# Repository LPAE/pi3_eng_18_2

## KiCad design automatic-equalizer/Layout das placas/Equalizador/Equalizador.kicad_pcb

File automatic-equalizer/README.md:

# Elaboração de um Sistema de Auto-Equalização Ambiente
O projeto proposto é um sistema de equalização sonora automática utilizando equalizadores analógicos cujos ganhos de cada banda são controlados por uma tensão proveniente de um microcontrolador. Esses ganhos irão variar conforme os aspectos mecânicos da sala, tais como material da parede e móveis posicionados em diferentes lugares, fazendo com que o espectro de frequências de áudio antes não linear em decorrência das perdas ocasionadas, se torne linear. O esquema inicial proposto ao projeto é o presente na Figura 1.

#### Figura 1 - Esquema inicial do projeto.

#### <i>A descrição completa do projeto está no arquivo [relatorio_final.pdf](https://github.com/BroeringFelipe/automatic-equalizer/blob/master/Relat%C3%B3rio%20do%20Projeto/Relat%C3%B3rio%20Final.pdf)</i>

### Bibliografia
ANALOG DEVICES: <b>Programmable Gain Amplifiers</b>. 2018. Disponível em: <https://www.analog.com/en/products/amplifiers/specialty-amplifiers/programmable-gain-amplifiers.html>. Acesso em: 14 dez. 2018.

TEXAS INSTRUMENTS: <b>Datasheet, PGA103 - Programmable Gain Amplifier</b>. 1993. Disponível em: <http://www.ti.com/lit/ds/sbos031/sbos031.pdf>. Acesso em: 14 dez. 2018.

FAIRCHILD Semiconductor Corporation:<b> A Linear Gain Controlled Amplifier, Amplication Note</b>. Rev. 1.0. 2015. Disponível em: <http://www.ti.com/lit/ds/sbos031/sbos031.pdf>. Acesso em: 14 dez. 2018.

CARTER,  B.;  MANCINI,  R.<b> Op  Amps  For  Everyone</b>.  3.  ed.  Burlington,  MA,  USA:  Elsevier,2004. 

RIBEIRO, Renan.<b> Desenvolvimento de um Equalizador Gráfico Digital de 10 Bandas</b>. 2017. 54 f. Trabalho de conclusão de curso (Curso de Engenharia de Computação) - Universidade Tecnológica Federal do Paraná, Pato Branco, 2017.

STMICROELECTRONICS TDA7294: <b>100V - 100W DMOS AUDIO AMPLIFIER WITH MUTE/ST-BY - Datasheet</b>. 2003. Disponível em: <https://www.st.com/resource/en/datasheet/cd00000017.pdf>. Acesso em: 11 dez. 2018.

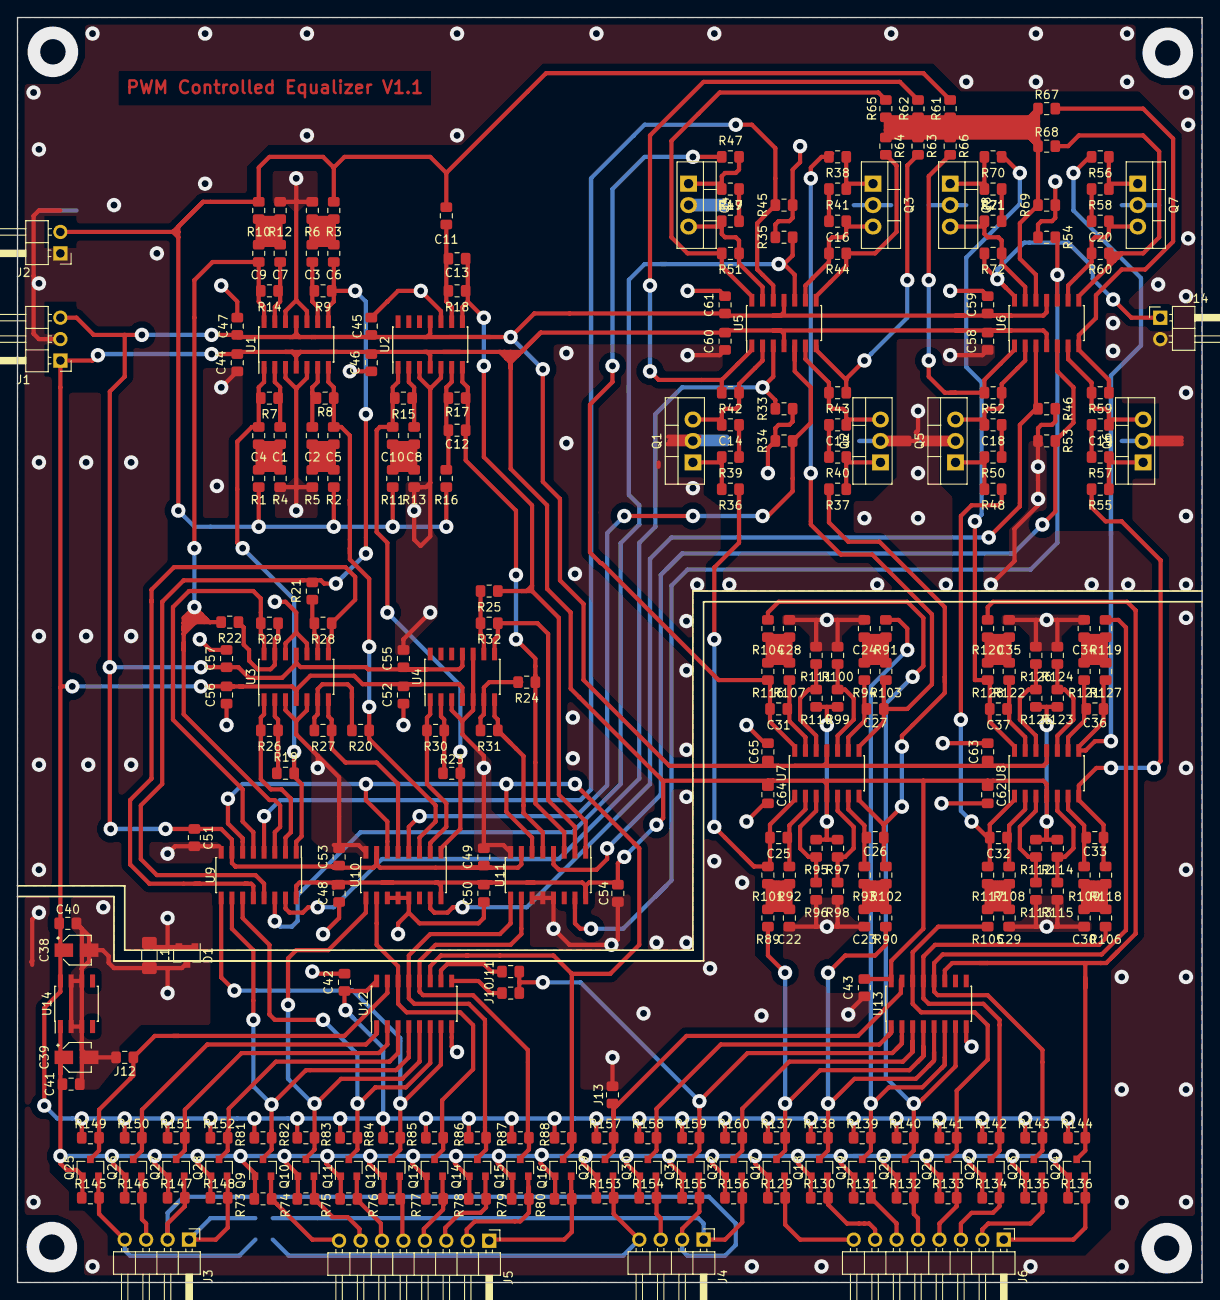
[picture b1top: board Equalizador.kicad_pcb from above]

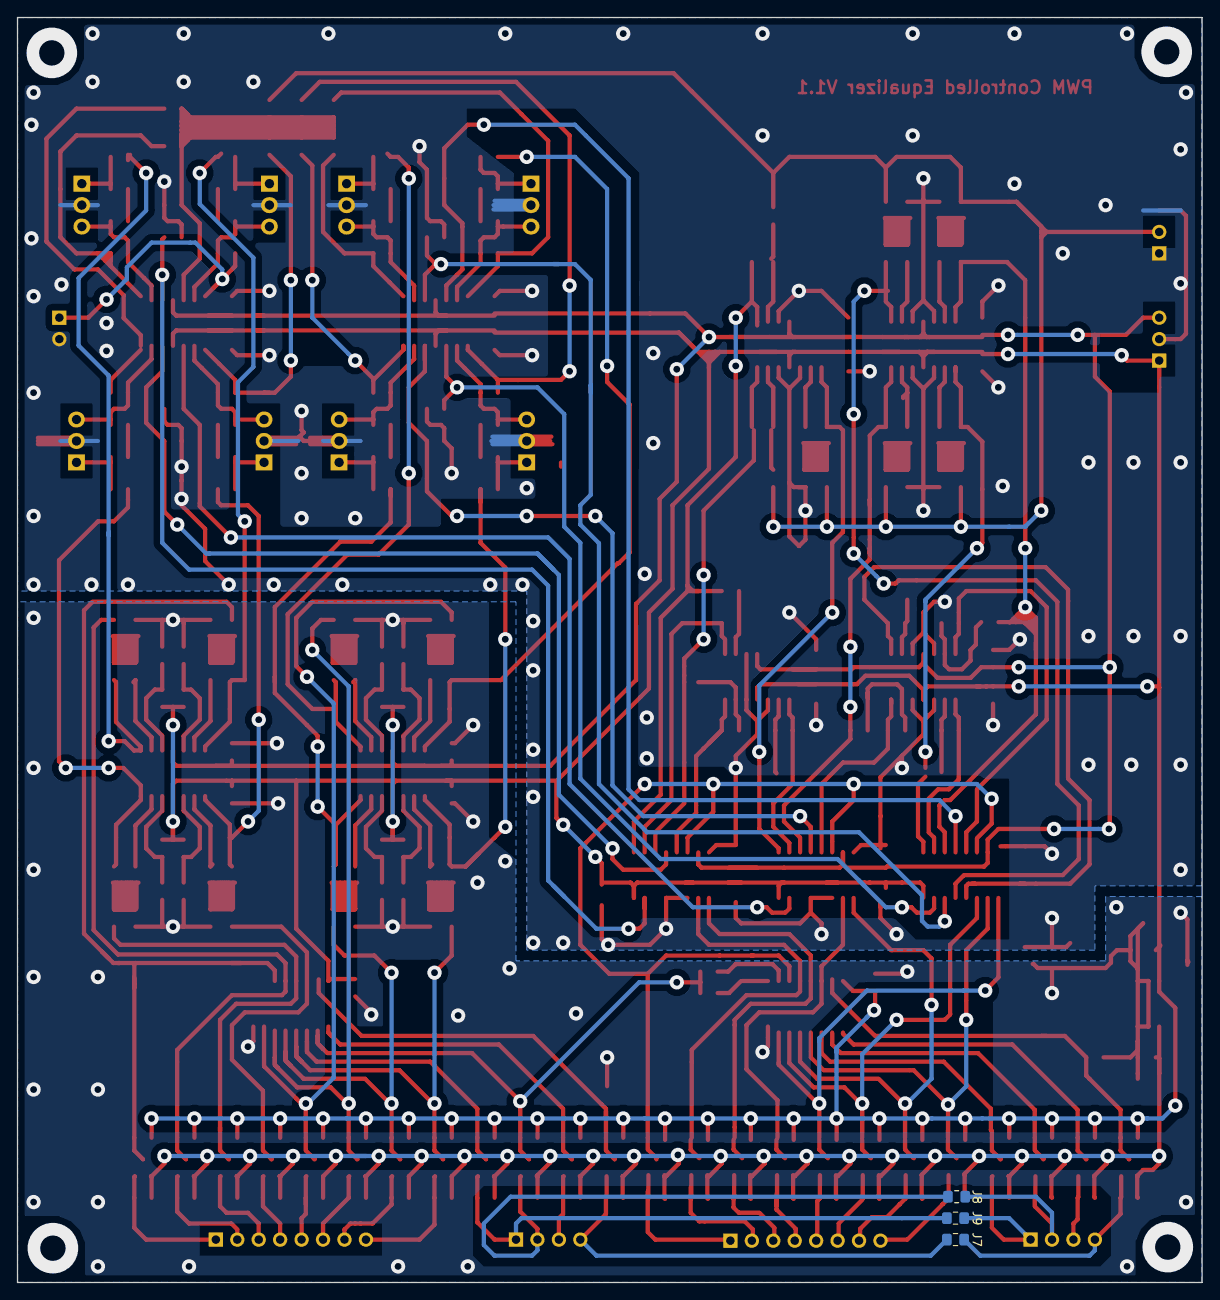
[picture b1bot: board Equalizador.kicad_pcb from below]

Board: 2 copper layers, 140.3 x 149.9 mm, 287 parts (3 on the bottom side), 161 nets.

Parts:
C1, C2, C3, C4, C5, C6, C7, C8, C9, C10, C11, C12, C13, C14, C15, C16, C17, C18, C19, C20, C21, C22, C23, C24, C25, C26, C27, C28, C29, C30, C31, C32, C33, C34, C35, C36, C37, C40, C41, C42, C43, C44, C45, C46, C47, C48, C49, C50, C51, C52, C53, C54, C55, C56, C57, C58, C59, C60, C61, C62, C63, C64, C65: C_Small; C_0805_2012Metric_Pad1.15x1.40mm_HandSolder
C38, C39: C_Small; CP_Elec_3x5.3
D1: BAT54S; SOT-23
J1: Conn_01x03; PinHeader_1x03_P2.54mm_Horizontal
J2, J14: Conn_01x02; PinHeader_1x02_P2.54mm_Horizontal
J3, J4: Conn_01x04; PinHeader_1x04_P2.54mm_Horizontal
J5, J6: Conn_01x08; PinHeader_1x08_P2.54mm_Horizontal
J7, J8, J9, J10, J11, J12, J13: Conn_02x01; R_0805_2012Metric_Pad1.15x1.40mm_HandSolder
L1: L_Small; L_1206_3216Metric_Pad1.42x1.75mm_HandSolder
Q1, Q2, Q3, Q4, Q5, Q6, Q7, Q8: BF245C; TO-220-3_Vertical
Q9, Q10, Q11, Q12, Q13, Q14, Q15, Q16, Q17, Q18, Q19, Q20, Q21, Q22, Q23, Q24, Q25, Q26, Q27, Q28, Q29, Q30, Q31, Q32: 2N7002; SOT-23
R1, R2, R3, R4, R5, R6, R7, R8, R9, R10, R11, R12, R13, R14, R15, R16, R17, R18, R33, R34, R35, R36, R37, R38, R39, R40, R41, R42, R43, R44, R45, R46, R47, R48, R49, R50, R51, R52, R53, R54, R55, R56, R57, R58, R59, R60, R61, R62, R63, R64, R65, R66, R67, R68, R69, R70, R71, R72, R73, R74, R75, R76, R77, R78, R79, R80, R81, R82, R83, R84, R85, R86, R87, R88, R89, R90, R91, R92, R93, R94, R95, R96, R97, R98, R99, R100, R101, R102, R103, R104, R105, R106, R107, R108, R109, R110, R111, R112, R113, R114, R115, R116, R117, R118, R119, R120, R121, R122, R123, R124, R125, R126, R127, R128, R129, R130, R131, R132, R133, R134, R135, R136, R137, R138, R139, R140, R141, R142, R143, R144, R145, R146, R147, R148, R149, R150, R151, R152, R153, R154, R155, R156, R157, R158, R159, R160: R_US; R_0805_2012Metric_Pad1.15x1.40mm_HandSolder
R19, R20, R21, R22, R23, R24, R25, R26, R27, R28, R29, R30, R31, R32: 10k; R_0805_2012Metric_Pad1.15x1.40mm_HandSolder
U1, U2, U3, U4, U5, U6, U7, U8: TL074; SOIC-14_3.9x8.7mm_P1.27mm
U9, U10, U11: 4053; SOIC-16_3.9x9.9mm_P1.27mm
U12, U13: 4094D; SOIC-16_3.9x9.9mm_P1.27mm
U14: L78L33_SO8; SOIC-8_3.9x4.9mm_P1.27mm

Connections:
+3V3: C39.1, C41.1, Q9.1, Q10.1, Q11.1, Q12.1, Q13.1, Q14.1, Q15.1, Q16.1, Q17.1, Q18.1, Q19.1, Q20.1, Q21.1, Q22.1, Q23.1, Q24.1, Q25.1, Q26.1, Q27.1, Q28.1, Q29.1, Q30.1, Q31.1, Q32.1, R73.1, R74.1, R75.1, R76.1, R77.1, R78.1, R79.1, R80.1, R129.1, R130.1, R131.1, R132.1, R133.1, R134.1, R135.1, R136.1, R145.1, R146.1, R147.1, R148.1, R153.1, R154.1, R155.1, R156.1, U14.1
+15V: C38.1, C40.1, C42.1, C43.1, C44.1, C46.1, C48.1, C50.1, C52.2, C54.2, C56.2, C58.1, C60.1, C62.1, C64.1, J1.1, R81.1, R82.1, R83.1, R84.1, R85.1, R86.1, R87.1, R88.1, R95.1, R97.1, R99.1, R110.1, R112.1, R114.1, R123.1, R125.1, R137.1, R138.1, R139.1, R140.1, R141.1, R142.1, R143.1, R144.1, R149.1, R150.1, R151.1, R152.1, R157.1, R158.1, R159.1, R160.1, U1.4, U2.4, U3.4, U4.4, U5.4, U6.4, U7.4, U8.4, U9.16, U10.16, U11.16, U12.16, U13.16, U14.8
-15V: C45.1, C47.1, C49.1, C51.1, C53.2, C55.2, C57.2, C59.1, C61.1, C63.1, C65.1, J1.3, U1.11, U2.11, U3.11, U4.11, U5.11, U6.11, U7.11, U8.11, U9.7, U10.7, U11.7
/Inversoras/Ctrl_inv_1: Q9.3, R81.2, U9.10, U12.4
/Inversoras/Ctrl_inv_2: Q10.3, R82.2, U10.9, U12.5
/Inversoras/Ctrl_inv_3: Q11.3, R83.2, U9.11, U12.6
/Inversoras/Ctrl_inv_4: Q12.3, R84.2, U9.9, U12.7
/Inversoras/Ctrl_inv_5: Q13.3, R85.2, U10.10, U12.14
/Inversoras/Ctrl_inv_6: Q14.3, R86.2, U11.9, U12.13
/Inversoras/Ctrl_inv_7: Q15.3, R87.2, U11.10, U12.12
/Inversoras/INH: Q16.3, R88.2, U9.6, U10.6, U11.6, U12.11
/Inversoras/Vin_1_1: C4.1, R7.1, R19.2, U1.1, U9.1
/Inversoras/Vin_2_1: C5.1, R8.1, R20.2, U1.7, U10.3
/Inversoras/Vin_3_1: C6.1, R9.1, R21.2, U1.8, U9.13
/Inversoras/Vin_4_1: C9.1, R14.1, R22.2, U1.14, U9.3
/Inversoras/Vin_5_1: C10.1, R15.1, R23.2, U2.1, U10.1
/Inversoras/Vin_6_1: C12.1, R17.1, R24.2, U2.7, U11.3
/Inversoras/Vin_7_1: C13.1, R18.1, R25.2, U2.8, U11.1
/Inversoras/Vinv_1: R26.1, U3.1, U9.2
/Inversoras/Vinv_2: R27.1, U3.7, U10.5
/Inversoras/Vinv_3: R28.1, U3.8, U9.12
/Inversoras/Vinv_4: R29.1, U3.14, U9.5
/Inversoras/Vinv_5: R30.1, U4.1, U10.2
/Inversoras/Vinv_6: R31.1, U4.7, U11.5
/Inversoras/Vinv_7: R32.1, U4.8, U11.2
/Somador/Ctrl_G: C37.1, R70.2, R128.1, U8.14
/Somador/Vin_1_3: R42.1, R62.2, U5.1
/Somador/Vin_2_3: R43.1, R63.2, U5.7
/Somador/Vin_3_3: R44.1, R64.2, U5.8
/Somador/Vin_4_3: R51.1, R65.2, U5.14
/Somador/Vin_5_3: R52.1, R66.2, U6.1
/Somador/Vin_6_3: R59.1, R67.2, U6.7
/Somador/Vin_7_3: R60.1, R68.2, U6.8
/Somador/Vout: J14.1, R72.1, U6.14
/VCA/Ctrl_G_1: C25.1, R36.2, R101.1, U7.1
/VCA/Ctrl_G_2: C26.1, R37.2, R102.1, U7.7
/VCA/Ctrl_G_3: C27.1, R38.2, R103.1, U7.8
/VCA/Ctrl_G_4: C31.1, R47.2, R116.1, U7.14
/VCA/Ctrl_G_5: C32.1, R48.2, R117.1, U8.1
/VCA/Ctrl_G_6: C33.1, R55.2, R118.1, U8.7
/VCA/Ctrl_G_7: C36.1, R56.2, R127.1, U8.8
/VCA/Vin_1_2: R33.1, U5.3, U9.15
/VCA/Vin_2_2: R34.1, U5.5, U10.4
/VCA/Vin_3_2: R35.1, U5.10, U9.14
/VCA/Vin_4_2: R45.1, U5.12, U9.4
/VCA/Vin_5_2: R46.1, U6.3, U10.15
/VCA/Vin_6_2: R53.1, U6.5, U11.4
/VCA/Vin_7_2: R54.1, U6.10, U11.15
/sheet5BB14968/OUT1: J12.1, Q25.3, R149.2, U12.15
/sheet5BB14968/OUT2: Q26.3, R150.2, U12.1
/sheet5BB14968/OUT3: Q27.3, R151.2, U12.2
/sheet5BB14968/OUT4: Q28.3, R152.2, U12.3
/sheet5BB62068/OUT1: Q17.3, R89.1, R137.2, U13.4
/sheet5BB62068/OUT2: Q18.3, R90.1, R138.2, U13.5
/sheet5BB62068/OUT3: Q19.3, R91.1, R139.2, U13.6
/sheet5BB62068/OUT4: Q20.3, R104.1, R140.2, U13.7
/sheet5BB62068/OUT5: Q21.3, R105.1, R141.2, U13.14
/sheet5BB62068/OUT6: Q22.3, R106.1, R142.2, U13.13
/sheet5BB62068/OUT7: Q23.3, R119.1, R143.2, U13.12
/sheet5BB62068/OUT8: Q24.3, R120.1, R144.2, U13.11
/sheet5BC68AAF/OUT1: J13.1, Q29.3, R157.2, U13.15
/sheet5BC68AAF/OUT2: Q30.3, R158.2, U13.1
/sheet5BC68AAF/OUT3: J10.2, J11.2, Q31.3, R159.2, U13.2
/sheet5BC68AAF/OUT4: Q32.3, R160.2, U13.3
Ctrl_Inv_1: J5.8, Q9.2, R73.2
Ctrl_Inv_2: J5.7, Q10.2, R74.2
Ctrl_Inv_3: J5.6, Q11.2, R75.2
Ctrl_Inv_4: J5.5, Q12.2, R76.2
Ctrl_Inv_5: J5.4, Q13.2, R77.2
Ctrl_Inv_6: J5.3, Q14.2, R78.2
Ctrl_Inv_7: J5.2, Q15.2, R79.2
Ctrl_Inv_8: J5.1, Q16.2, R80.2
Ctrl_Inv_CLK: J3.1, J9.1, Q28.2, R148.2
Ctrl_Inv_DATA: J3.2, J8.1, Q27.2, R147.2
Ctrl_Inv_OE: J3.4, J7.1, Q25.2, R145.2
Ctrl_Inv_STR: J3.3, Q26.2, R146.2
GND: C44.2, C45.2, C46.2, C47.2, C48.2, C49.2, C50.2, C51.2, C52.1, C53.1, C54.1, C55.1, C56.1, C57.1, C58.2, C59.2, C60.2, C61.2, D1.1, D1.2, J1.2, J2.1, J14.2, L1.1, Q1.2, Q2.2, Q3.2, Q4.2, Q5.2, Q6.2, Q7.2, Q8.2, R4.1, R5.1, R6.1, R12.1, R13.1, R33.2, R34.2, R35.2, R45.2, R46.2, R53.2, R54.2, R69.2, U1.3, U1.5, U1.10, U1.12, U2.3, U2.5, U2.10, U3.3, U3.5, U3.10, U3.12, U4.3, U4.5, U4.10, U9.8, U10.8, U10.11, U10.12, U10.13, U11.8, U11.11, U11.12, U11.13
GNDD: C22.1, C23.1, C24.1, C28.1, C29.1, C30.1, C34.1, C35.1, C38.2, C39.2, C40.2, C41.2, C42.2, C43.2, C62.2, C63.2, C64.2, C65.2, D1.3, J12.2, J13.2, L1.2, R96.2, R98.2, R100.2, R111.2, R113.2, R115.2, R124.2, R126.2, U12.8, U13.8, U14.2, U14.3, U14.6, U14.7
unnamed: C1.1, R7.2, U1.2
unnamed: C1.2, C4.2, R1.2, R4.2
unnamed: C2.1, R8.2, U1.6
unnamed: C2.2, C5.2, R2.2, R5.2
unnamed: C3.1, R9.2, U1.9
unnamed: C3.2, C6.2, R3.2, R6.2
unnamed: C7.1, R14.2, U1.13
unnamed: C7.2, C9.2, R10.2, R12.2
unnamed: C8.1, R15.2, U2.2
unnamed: C8.2, C10.2, R11.2, R13.2
unnamed: C11.1, C13.2, R18.2, U2.9
unnamed: C12.2, R16.2, R17.2, U2.6
unnamed: C14.1, Q1.3, R42.2, U5.2
unnamed: C14.2, R39.1
unnamed: C15.1, Q2.3, R43.2, U5.6
unnamed: C15.2, R40.1
unnamed: C16.1, Q3.3, R44.2, U5.9
unnamed: C16.2, R41.1
unnamed: C17.1, Q4.3, R51.2, U5.13
unnamed: C17.2, R49.1
unnamed: C18.1, Q5.3, R52.2, U6.2
unnamed: C18.2, R50.1
unnamed: C19.1, Q6.3, R59.2, U6.6
unnamed: C19.2, R57.1
unnamed: C20.1, Q7.3, R60.2, U6.9
unnamed: C20.2, R58.1
unnamed: C21.1, Q8.3, R72.2, U6.13
unnamed: C21.2, R71.1
unnamed: C22.2, R89.2, R92.2, R101.2
unnamed: C23.2, R90.2, R93.2, R102.2
unnamed: C24.2, R91.2, R94.2, R103.2
unnamed: C25.2, R92.1, U7.2
unnamed: C26.2, R93.1, U7.6
unnamed: C27.2, R94.1, U7.9
unnamed: C28.2, R104.2, R107.2, R116.2
unnamed: C29.2, R105.2, R108.2, R117.2
unnamed: C30.2, R106.2, R109.2, R118.2
unnamed: C31.2, R107.1, U7.13
unnamed: C32.2, R108.1, U8.2
unnamed: C33.2, R109.1, U8.6
unnamed: C34.2, R119.2, R121.2, R127.2
unnamed: C35.2, R120.2, R122.2, R128.2
unnamed: C36.2, R121.1, U8.9
unnamed: C37.2, R122.1, U8.13
unnamed: J10.1, U12.9
unnamed: J11.1, U12.10
unnamed: Q1.1, R36.1, R39.2
unnamed: Q2.1, R37.1, R40.2
unnamed: Q3.1, R38.1, R41.2
unnamed: Q4.1, R47.1, R49.2
unnamed: Q5.1, R48.1, R50.2
unnamed: Q6.1, R55.1, R57.2
unnamed: Q7.1, R56.1, R58.2
unnamed: Q8.1, R70.1, R71.2
unnamed: R19.1, R26.2, U3.2
unnamed: R20.1, R27.2, U3.6
unnamed: R21.1, R28.2, U3.9
unnamed: R22.1, R29.2, U3.13
unnamed: R23.1, R30.2, U4.2
unnamed: R24.1, R31.2, U4.6
unnamed: R25.1, R32.2, U4.9
unnamed: R61.1, R62.1, R63.1, R64.1, R65.1, R66.1, R67.1, R68.1, R69.1, U6.12
unnamed: R95.2, R96.1, U7.3
unnamed: R97.2, R98.1, U7.5
unnamed: R99.2, R100.1, U7.10
unnamed: R110.2, R111.1, U7.12
unnamed: R112.2, R113.1, U8.3
unnamed: R114.2, R115.1, U8.5
unnamed: R123.2, R124.1, U8.10
unnamed: R125.2, R126.1, U8.12
PWM_1: J6.8, Q17.2, R129.2
PWM_2: J6.7, Q18.2, R130.2
PWM_3: J6.6, Q19.2, R131.2
PWM_4: J6.5, Q20.2, R132.2
PWM_5: J6.4, Q21.2, R133.2
PWM_6: J6.3, Q22.2, R134.2
PWM_7: J6.2, Q23.2, R135.2
PWM_8: J6.1, Q24.2, R136.2
PWM_CLK: J4.1, J9.2, Q32.2, R156.2
PWM_DATA: J4.2, J8.2, Q31.2, R155.2
PWM_OE: J4.4, J7.2, Q29.2, R153.2
PWM_STR: J4.3, Q30.2, R154.2
Vin: C11.2, J2.2, R1.1, R2.1, R3.1, R10.1, R11.1, R16.1, R61.2

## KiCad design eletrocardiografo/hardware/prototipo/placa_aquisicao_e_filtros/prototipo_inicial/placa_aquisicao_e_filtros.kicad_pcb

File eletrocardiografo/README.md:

# Eletrocardiógrafo

Projeto para a disciplina PIN22107 do curso de Graduação em Engenharia Eletrônica do Instituto Federal de Santa Catarina. Consiste na concepção e execução de um eletrocardiógrafo de baixo consumo energético capaz de adquirir um sinal de eletrocardiograma por meio de 3 eletrodos e enviar suas medições para um aplicativo de aparelho celular.

## Especificações de projeto
* Energizado por bateria, portanto apresentando baixo consumo energético.

* Capaz de medir sinais entre 0,05 e 100 Hz, permitindo visualização e análise da morfologia do sinal cardíaco humano com propriedade.

## Etapas do projeto
* **Aquisição do sinal:** Por meio de eletrodos conectados ao paciente, verificando e garantindo a proteção do mesmo, com processo de isolamento do sistema. Os sinais obtidos diretamente dos eletrodos tem amplitude reduzida, atingindo 1 mV com uma frequência na faixa entre 0,05 e 100 Hz. Desse modo, para uma melhor visualização e manipulação, uma etapa de amplificação é necessária, tomando cuidado com a rejeição de ruído de modo comum.

* **Filtros:** Um filtro passa faixa deve ser implementado para seleção da banda de operação desejada, podendo ser composto por um passa altas em série com um passa baixas e, além disso, deve-se atentar para o fato de que a frequência da rede elétrica pode interferir no sinal e, portanto, deve ser removida por meio de um filtro rejeita faixa, com alto fator de qualidade.

* **Adequação do sinal:** Além de um ajuste de offset, é necessário implementar um controle de ganho que adeque a amplitude do sinal, preparando-o para digitalização por meio de um ADC.

* **Digitalização:**  A conversão do sinal analógico para digital pode ser realizada através de um conversor dedicado ou até mesmo por meio do conversor integrado de algum microcontrolador, como por exemplo o ATMEGA328p.

* **Processamento digital:** Envio dos dados via Bluetooth para o aplicativo de celular.

## Fluxograma
Para uma melhor organização e visualização das etapas necessárias, foi construído o seguinte fluxograma:

## Aquisição do sinal
Contando com um amplificador de instrumentação de alta relação sinal-ruído (SNR), o estágio inicial de amplificação faz a leitura do sinal diferencial entre os eletrodos esquerdo e direito, ao mesmo tempo que injeta uma referência por meio de um terceiro eletrodo conectado ao paciente.

O esquemático do circuito utilizado nesse estágio pode ser verificado a seguir, sendo baseado no circuito proposto e verificado na folha de dados do próprio fabricante:

## Filtros
Os filtros passa-baixas, passa-altas e rejeita-faixa foram projetados conforme o equacionamento descrito pelo livro "Amplificadores Operacionais e Filtros Ativos". As simulações foram realizadas no _software_ LTspice XVII. Foi definido inicialmente ganho unitário para todos os filtros.

### Passa-altas
Projetou-se o filtro passa-altas com ganho unitário na estrutura _voltage-controlled voltage source_ (VCVS).

Por meio do uso do software de simulação, o comportamento resultante do filtro é:

### Passa-baixas
Abaixo é possível seguir a sequência de passos utilizados na construção do filtro passa-baixas:

No intuito de otimizar a eficiência energética do eletrocardiógrafo, foi analisada a possibilidade de implementar um filtro passa-baixas passivo, portanto foi realizada uma comparação entre o filtro projetado de 2ª ordem com um filtro passivo na simulação.

Apesar da economia de componentes apresentada pelo filtro passivo, sua atenuação na banda passante é indesejada e, portanto, optou-se pela utilização do filtro de 2ª ordem, que apresenta ainda decaimento de 40 dB por década na rejeição e consequentemente um fator de qualidade mais elevado.

### Rejeita-faixa

Inicialmente, projetou-se o filtro notch ativo para rejeitar ruídos oriundos da rede elétrica de 60 Hz.

Entretanto, devido à sensibilidade deste filtro aos valores dos componentes utilizados, e a necessidade de um elevado fator de qualidade, concluiu-se que implementá-lo digitalmente seria uma alternativa mais apropriada. Além disso, pelo fato do circuito ser alimentado via bateria, a interferência da rede é fortemente reduzida, embora não completamente eliminada.

## Automatic Gain Control (AGC)

Ao longo do projeto, verificou-se que seria interessante a implementação de um ajuste de ganho automático devido à incerteza na amplitude do sinal de entrada, já que o mesmo varia conforme o biotipo do paciente e disposição dos eletrodos, possibilitando que a amplificação seja insuficiente ou demasiada.

Após analisar e estudar diversas maneiras de implementar um sistema de adequação do sinal, buscando obter uma excursão adequada e constante para diferentes amplitudes de entrada, surgiu como uma solução conveniente a ideia de um controle de ganho automático (AGC) por meio de um amplificador operacional não-inversor com a resistência de um JFET participando de sua realimentação negativa e influenciando diretamente em seu ganho de amplificação.

Embora seja possível controlar a resistência do JFET apropriadamente através da aplicação de um PWM gerado pelo microcontrolador que adquire o sinal, isso exige mais processamento do mesmo e consequentemente eleva seu consumo energético. Sendo assim, a alternativa escolhida foi a de controlar esse sistema de maneira analógica.

Com o auxílio do LTSpice, traçou-se, em simulação, a curva da resistência Rds em função da tensão Vgs do BF245B, transistor selecionado para o circuito.

É notável a grande variação em sua resistência que ocorre em um pequeno intervalo de variação de Vgs. Devido a isso, percebe-se que é por volta desse intervalo que o JFET deve operar. Logo, projetou-se um circuito para fechar a malha de realimentação do AGC, constituído de um retificador de precisão inversor com ajuste de ganho, que detecta e inverte a tensão de pico positiva do sinal, mantendo o valor negativo obtido, utilizado para controlar o estrangulamento no canal do transistor, controlando sua condutividade. 

O ajuste de ganho da realimentação, proporcionado pelo trimpot RV1, permite que se encontre o ponto ideal de operação do BF245B e também possibilita a definição de um valor limite para o sinal amplificado pelo AGC.

## Somador

Na intenção de adequar o sinal de saída para uma conversão AD fez com que surgisse a necessidade de inserir um deslocamento de nível no sinal de saída, o deixando completamente positivo. A maneira mais eficiente encontrada faz o uso de um circuito somador não-inversor, visto na figura a seguir:

Mesmo que várias fontes tratem o circuito inversor como mais indicado e até mesmo mais difundido, a escolha pela utilização de um somador não-inversor procurou manter a ideia de um estágio genérico entre os outros, sem levar em conta se o sinal que entrava nele era invertido ou não, já que a presença de um sinal invertido na saída pode ser corrigida com a simples inversão dos conectores dos eletrodos.

Outra parte importante no projeto do somador se deu pela adição de dois resistores de alto valor (1 Megaohm), de maneira a proporcionar um casamento entre as impedâncias de saída do AGC (a própria impedância de saída do amplificador utilizado) e a de entrada do somador (entrada do amplificador empregado).

## Hardware

* **Protótipo inicial**

Em um primeiro momento, para validar os circuitos projetados até aquele momento, optou-se pela confecção de um protótipo contendo apenas os estágios de aquisição e filtragem do sinal. Já na intenção de condicioná-lo para uma conversão AD, por meio de um microcontrolador, existiu a necessidade de um ajuste de _offset_, tornando o sinal de saída completamente positivo. 

A alternativa aparentemente mais prática e econômica foi a de inserir esse acréscimo no valor de tensão já no próprio filtro passa-altas, considerando que a topologia de um filtro ativo MFB (_Multiple Feedback_) permite um deslocamento do nível de tensão apenas injetando a tensão desejada na entrada não-inversora do amplificador operacional envolvido no circuito. Ao contrário do esperado, o _offset_ não se comportou corretamente, pois mesmo com ganho unitário nos filtros seguintes, o sinal de saída apresentou grande instabilidade.

Além disso, o ajuste de ganho do sistema foi inserido por meio de um potenciômetro em série com o resistor de ganho do AD620. Observou-se, entretanto, que essa topologia deixa a desejar pelos valores de ganho muito elevados para esse estágio, já que nele o sinal ainda não foi filtrado e portanto componentes em frequências indesejadas também são amplificadas.

Para ilustrar, a seguir, é possível ver o esquemático que descreve o circuito utilizado no protótipo inicial:

Percebe-se que o circuito é energizado por uma alimentação simétrica de 9V, proveniente de duas baterias. Ainda, abaixo é possível ver o layout da placa de circuito impresso resultante:

* **Placa final**

Levando em conta os problemas encontrados no protótipo inicial, a solução adotada com relação ao _offset_ foi de aplicá-lo em um estágio próprio, consistindo de um somador não-inversor, só no final do circuito, evitando que esse deslocamento de nível de tensão atrapalhasse o funcionamento das etapas anteriores, como os filtros e o próprio AGC.

Pensando no consumo energético e estabilidade do sistema, foi estabelecido que todos os circuitos seriam energizados com alimentação simétrica regulada de 3.3V. Por conseguinte, foi introduzida uma regulação da tensão de alimentação positiva utilizando o regulador linear _low-dropout_ LM1117. Em sequência, visando praticidade, projetou-se a obtenção da tensão de alimentação negativa através do inversor TPS60401. Isso flexibilizou o sistema com relação a sua tensão de entrada, podendo ser energizado por uma única bateria de valor de tensão entre 4.75 e 10V.

Outro ponto importante na construção e adequação do funcionamento da nova placa desenvolvida, consistiu na seleção dos ganhos envolvidos em cada etapa de maneira a manter um valor final de amplificação equilibrado que não trouxesse instabilidade ao conjunto. Um exemplo disso foi o ganho definido para o estágio do amplificador de instrumentação.

Por apresentar uma característica de amplificação com alta relação sinal-ruído (SNR), pareceu interessante o estabelecimento do maior ganho possível nesse estágio, de maneira a eliminar ao máximo o ruído do sinal adquirido. A seleção do ganho do circuito de aquisição é diretamente dependente do valor de resistência selecionado para o resistor R9, entre os pinos 1 e 8 do AD620 (estágio de aquisição). Na intenção de deixar o sistema independente de um ajuste manual, antes regulado pelo potenciômetro adicionado, a ideia passou a ser de fixar o valor desse resistor, inicialmente 75 ohms, resultando em um ganho próximo a 660. 

Com esse ganho estabelecido, a aquisição do sinal se deu de maneira eficiente, apresentando uma boa amplitude para o sinal de saída e uma satisfatória atenuação do ruído envolvido. Com a adição dos filtros, o sinal de saída alcançou as características desejadas para o circuito.

A partir da decisão de adicionar o estágio de controle de ganho, este proporcionou certas limitações em relação ao sinal condicionado pelos primeiros estágios: com um funcionamento adequado do AGC apenas para sinais de entrada com valores de tensão entre 50 e 500 mVpp, o ganho definido para o estágio de aquisição se tornou absurdo, já que o sinal fornecido ao estágio de controle automático de ganho já se encontrava fora dos limites determinados, deixando o sinal de saída instável e oscilando entre as saturações negativa e positiva do amplificador operacional, demonstrando um valor exagerado de amplificação.

Desse modo, ajustes foram feitos e um novo resistor tomou o lugar do R9, com valor igual a 1 kohms, resultando em um ganho próximo a 50 e permitindo que o ganho excedente necessário fosse proporcionado pelo próprio AGC. Com estes ajustes, os problemas de saturação foram corrigidos e o pleno funcionamento do estágio do AGC foi alcançado.
Funcionando como esperado, o somador não-inversor adicionado ao final cumpriu plenamente seu papel, resultando em uma saída do eletrocardiógrafo limitada a um valor de aproximadamente 1 Vpp e um _offset_ também de 1 VCC, adequado à janela estabelecida de 3.3 V limitados pela alimentação do sistema, que também acaba ditando o valor máximo de tensão para o ADC.

Por fim, o resultado foi uma placa de circuito impresso, empregando dessa vez alguns componentes do tipo SMD disponíveis para o projeto, de maneira a distribuí-los melhor e diminuir o tamanho físico de placa necessário para a construção do projeto.

## Software

Depois de todo o processo de construção do eletrocardiógrafo, dispositivo preocupado em evidenciar o formato do sinal emitido pela pulsação cardiovascular, é importante encontrar uma maneira de mostrar graficamente a saída do conjunto. Para esta tarefa, a escolha de uma conexão por meio de um transmissor Bluetooth visou a praticidade de uma conexão sem fio e também por ser uma ferramenta democrática, já que todos os smartphones atuais contam com esse tipo de conexão, o que leva à criação de um produto de mais fácil utilização e adaptação.

O transmissor Bluetooth escolhido para a tarefa é um módulo do tipo HC-05, que utiliza a comunicação UART do microcontrolador para receber e enviar informações do mesmo. Para a visualização gráfica, foi utilizado um aplicativo para smartphones com sistema operacional Android, gratuito, e facilmente encontrado na loja de aplicativos. Nesse aplicativo, o envio de uma _string_ contendo o valor lido no ADC em um formato reconhecido pelo software permitiu que a onda fosse visualizada de maneira bem prática.  

## Resultados

Depois de toda a etapa de projeto, é importante a validação dos resultados esperados, verificando se os objetivos do projeto foram alcançados. 

Na figura a seguir, é possível verificar o sinal de saída do eletrocardiógrafo, obtido com o auxílio de um osciloscópio:

O sinal visto na imagem acima traz algumas informações importantes sobre as validações do projeto: primeiramente, é possível ver um sinal de mais alta frequência sobreposto ao do ECG, este que é a influência eletromagnética causada pela própria rede de distribuição, com sua frequência de 60 Hz, e que acaba afetando o circuito que é eletromagneticamente sensível. Além disso, frequências muito mais altas podem ser verificadas sobre o sinal, na ordem dos MHz, provenientes de ondas de radiofrequência que transitam pelo ambiente e que não conseguem ser filtradas.

A presença da frequência de 60 Hz na saída do circuito era esperada, já que esta se encontra na faixa de operação do sistema (0.05 - 100 Hz), e deveria ser eliminada pelo filtro rejeita-faixa idealizado anteriormente mas que, por sua alta precisão de projeto, se tornou inviável. Parte dessa interferência já é diminuída por conta do uso de baterias para a alimentação do circuito, isolando o circuito de ruídos conduzidos, entretanto, não o blindando de possíveis ruídos irradiados. Na parte da medição, o uso de um osciloscópio desligado da rede, também alimentado por baterias, permitiu a visualização do sinal também com menor interferência.

No caso das componentes de mais alta frequência, idealmente, essas deveriam ser eliminadas pelo filtro passa-baixas implementado, evitando essa interferência. O que acontece, é que na prática o amplificador operacional utilizado nos filtros não é capaz de trabalhar em frequências muito altas, como as presentes no sinal. O modelo que usamos para a implementação (LM324) tem um bom funcionamento para frequências até a ordem de algumas centenas de kHz, no máximo poucos MHz, o que o deixa impossibilitado de eliminar as frequências indesejadas. Por questão de esclarecimento, foi testado isoladamente o filtro passa-baixas e verificado que sua frequência de corte se encontra nos 100 Hz esperados e que os ruídos decorrem mesmo da não-idealidade do amplificador operacional. 

Com a praticidade do osciloscópio, independente da rede de energia, foi possível desligar os outros equipamentos ligados nos arredores da montagem, verificando o nível de interferência de sua emissão de ondas eletromagnéticas. Ainda, o uso de um limitador de banda do osciloscópio, com o intuito de facilitar a visualização, eliminando as frequências que o próprio circuito era incapaz de lidar, resultou na imagem a seguir:

Em relação ao sinal visualizado por meio do aplicativo, empregando uma conexão Bluetooth, pode ser vista a seguir uma captura da tela do smartphone utilizado:

O sinal verificado no aplicativo não apresenta as componentes de frequência da ordem dos MHz, isso por conta da própria taxa de amostragem do sinal e da transmissão do Bluetooth, que acabam por “alisar” a curva.

## Consumo energético

O consumo da placa final de aquisição e condicionamento do sinal é estimado em aproximadamente 135.9mW. Esse valor representa o “pior caso”, pois foi obtido considerando: o consumo máximo de 1,2mA em cada canal dos LM324, incluindo os dois não utilizados; a corrente máxima de 1,3mA do AD620; a potência dissipada no regulador LM1119, considerando a bateria de 9V utilizada nos testes; e a eficiência de cerca de 97,5% do inversor TPS60401, apresentada quando o mesmo opera em 3,3V suprimindo as correntes de alimentação mencionadas para os amplificadores operacionais e de instrumentação.

Analisando à parte a potência dissipada pela parte digital do sistema, verifica-se que o microcontrolador ATmega328p consome cerca de 16,5mW operando ativamente em 16MHz e alimentado com +3,3V. Já o módulo bluetooth apresenta consumo médio de 82,5mW.

Considerando uma bateria de 9V comum, fornecendo uma quantidade de energia próxima a 500mAh, seria possível alimentar o circuito responsável pela aquisição e condicionamento do sinal (sem a transmissão bluetooth) por até 33 horas ininterruptas, com esse tempo podendo aumentar significativamente ao usar baterias com maior capacidade. Se o microcontrolador e módulo bluetooth forem considerados, o funcionamento ininterrupto sob as condições mencionadas chega a 19 horas.

## Sugestões para trabalhos futuros

* Naturalmente, algumas melhorias podem ser feitas a fim de se conseguir melhores resultados com o circuito implementado: para diminuir a interferência do sinal oscilatório de 60 Hz, proveniente da rede, seria possível a implementação de um filtro rejeita-faixa digital, utilizando o próprio microcontrolador que nesse momento faz apenas o trabalho da transmissão Bluetooth;

* Como maneira de blindar o circuito contra as interferências eletromagnéticas, a construção do circuito envolvido por um gabinete metálico traria melhores resultados, minimizando tanto a interferência da rede elétrica quanto as altas frequências que conseguem passar pelos filtros.

* O consumo energético pode ser minimizado ainda mais com a utilização de baterias de tensão próxima à mínima suportada, redução da frequência de operação do microcontrolador, bem como desabilitação de seus periféricos não utilizados e possivelmente utilização do modo _sleep_ entre leituras do ADC e envio de dados via bluetooth.

## Autores
* João Vitor Bassani
* Ricardo Schons Cirio

## Bibliografia
1. PERTENCE Jr., A. **Amplificadores Operacionais e Filtros Ativos**. 7.ed. Porto Alegre: Artmed, 2012.

2. SEDRA, A. S; SMITH, K. C. **Microeletrônica**. 5 ed. São Paulo: Pearson / Prentice Hall, 2010.

3. BOYLESTAD, R. e NASHELSKY, L. **Dispositivos eletrônicos e teoria de circuitos**. 8 ed. Prentice Hall do Brasil. Rio de Janeiro. 2005.

4. Analog Devices. **AD620**. Disponível em: <https://www.analog.com/media/en/technical-documentation/data-sheets/AD620.pdf>. Acesso em 16/12/2018.

5. On Semiconductor. **LM324**. Disponível em: <https://www.onsemi.com/pub/Collateral/LM324-D.PDF>. Acesso em 16/12/2018.

6. Texas Instruments. **LM1117**. Disponível em: <http://www.ti.com/lit/ds/symlink/lm1117.pdf>. Acesso em 16/12/2018.

7. Texas Instruments. **TPS6040x**. Disponível em: <http://www.ti.com/lit/ds/symlink/tps60400.pdf>. Acesso em 16/12/2018.

8. Atmel. **ATmega328P**. Disponível em: <http://ww1.microchip.com/downloads/en/DeviceDoc/Atmel-7810-Automotive-Microcontrollers-ATmega328P_Datasheet.pdf>. Acesso em 16/12/2018.

9. Makezine. **HC Serial Bluetooth Products**. Disponível em: <https://cdn.makezine.com/uploads/2014/03/hc_hc-05-user-instructions-bluetooth.pdf>. Acesso em 16/12/2018.

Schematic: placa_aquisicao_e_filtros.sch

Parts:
C1: 100p; C_Disc_D6.0mm_W2.5mm_P5.00mm
C2: 47n; C_Disc_D6.0mm_W2.5mm_P5.00mm
C3: 100n; C_Disc_D6.0mm_W2.5mm_P5.00mm
C4, C5, C6: 47u; C_Disc_D6.0mm_W2.5mm_P5.00mm
J1: Conn_01x04; PinHeader_1x04_P2.54mm_Vertical
J3: Conn_01x02; PinHeader_1x02_P2.54mm_Vertical
J4: Conn_02x04_Counter_Clockwise; PinHeader_2x04_P2.54mm_Vertical
R1: 1M; R_Axial_DIN0207_L6.3mm_D2.5mm_P10.16mm_Horizontal
R2: 10k; R_Axial_DIN0207_L6.3mm_D2.5mm_P10.16mm_Horizontal
R3, R4: 24.9k; R_Axial_DIN0207_L6.3mm_D2.5mm_P10.16mm_Horizontal
R5: 75R; R_Axial_DIN0207_L6.3mm_D2.5mm_P10.16mm_Horizontal
R6, R12: 18k; R_Axial_DIN0207_L6.3mm_D2.5mm_P10.16mm_Horizontal
R7: 30k; R_Axial_DIN0207_L6.3mm_D2.5mm_P10.16mm_Horizontal
R8: 33k; R_Axial_DIN0207_L6.3mm_D2.5mm_P10.16mm_Horizontal
R9: 150k; R_Axial_DIN0207_L6.3mm_D2.5mm_P10.16mm_Horizontal
R11: 130k; R_Axial_DIN0207_L6.3mm_D2.5mm_P10.16mm_Horizontal
RV1: 1k; Potentiometer_Piher_PC-16_Single_Horizontal
U1: Opamp_Quad_Generic; DIP-14_W7.62mm
U2: AD620; DIP-8_W7.62mm

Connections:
+9V: J4.1, J4.2, R11.1, U1.4 (V+), U2.7 (Vs+)
-9V: J4.5, J4.6, U1.11 (V-), U2.4 (Vs-)
GNDA: C2.2, J1.3, J3.2, J4.3, J4.4, J4.7, J4.8, R8.1, R12.2, U1.5 (+), U2.5 (Ref)
unnamed: C1.1, R2.2
unnamed: C2.1, R7.1, U1.12 (+)
unnamed: C3.2, R6.1, R7.2
unnamed: C4.1, C5.2, C6.2, R8.2
unnamed: C5.1, R9.1, U1.2 (-)
unnamed: R1.1, R2.1, R3.2, R4.1, U1.6 (-)
unnamed: R3.1, RV1.2, RV1.3, U2.8 (Rg)
unnamed: R4.2, R5.2, U2.1 (Rg)
unnamed: R5.1, RV1.1
unnamed: R11.2, R12.1, U1.3 (+)
left_electrode: J1.1, U2.2 (-)
out1: C4.2, U2.6
out2: C6.1, R6.2, R9.2, U1.1
out3: C3.1, J3.1, U1.13 (-), U1.14
ref_electrode: C1.2, J1.4, R1.2, U1.7
right_electrode: J1.2, U2.3 (+)

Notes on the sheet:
Amplificador de Instrumentação
Filtro passa-altas
Filtro passa-baixas

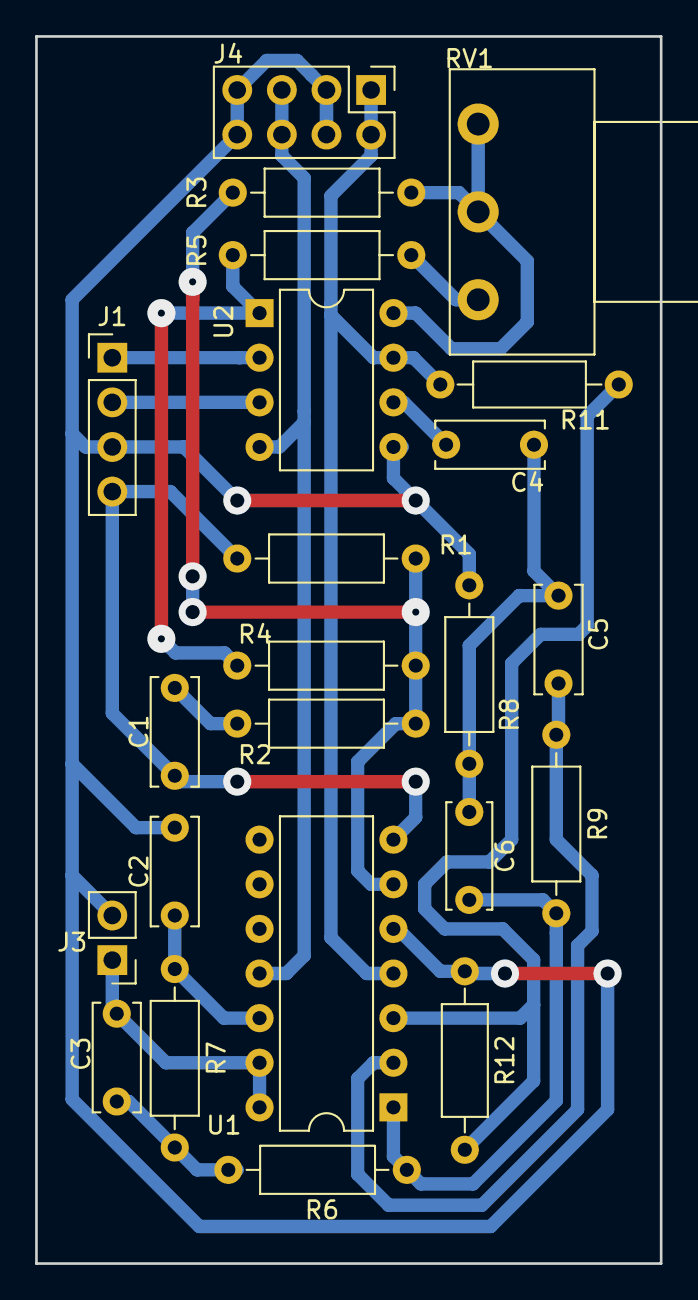
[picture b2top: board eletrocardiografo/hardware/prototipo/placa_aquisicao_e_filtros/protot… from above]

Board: 2 copper layers, 35.6 x 69.8 mm, 23 parts (0 on the bottom side), 19 nets.

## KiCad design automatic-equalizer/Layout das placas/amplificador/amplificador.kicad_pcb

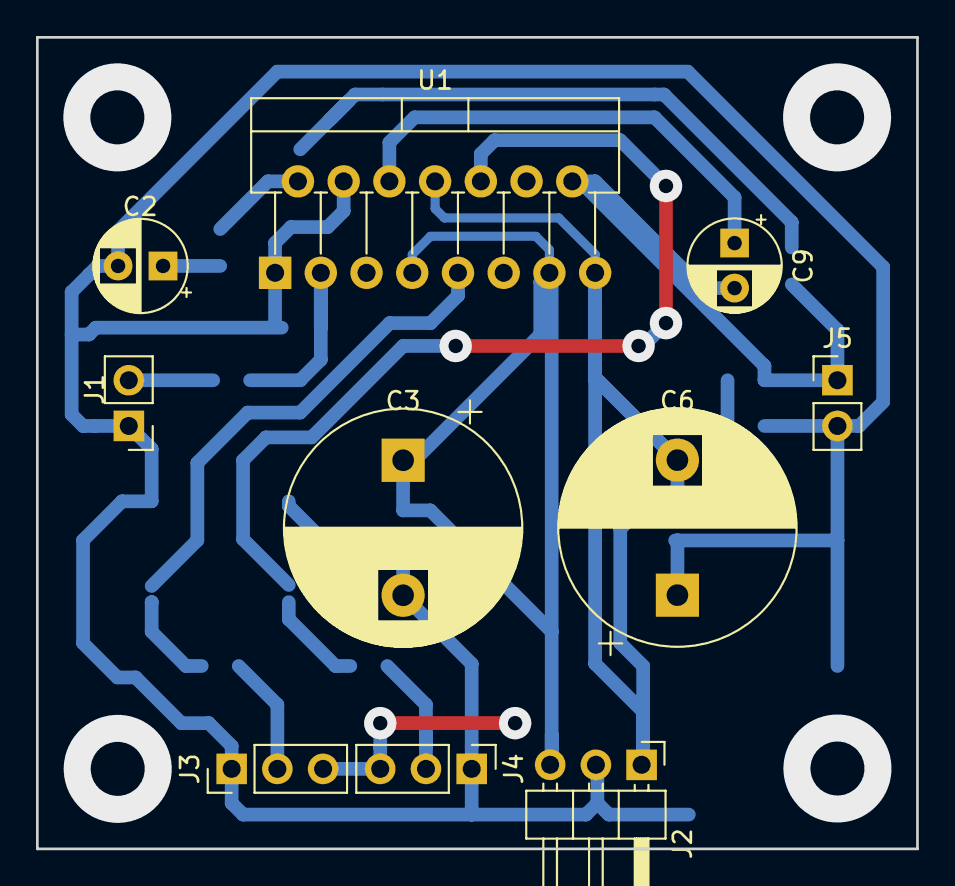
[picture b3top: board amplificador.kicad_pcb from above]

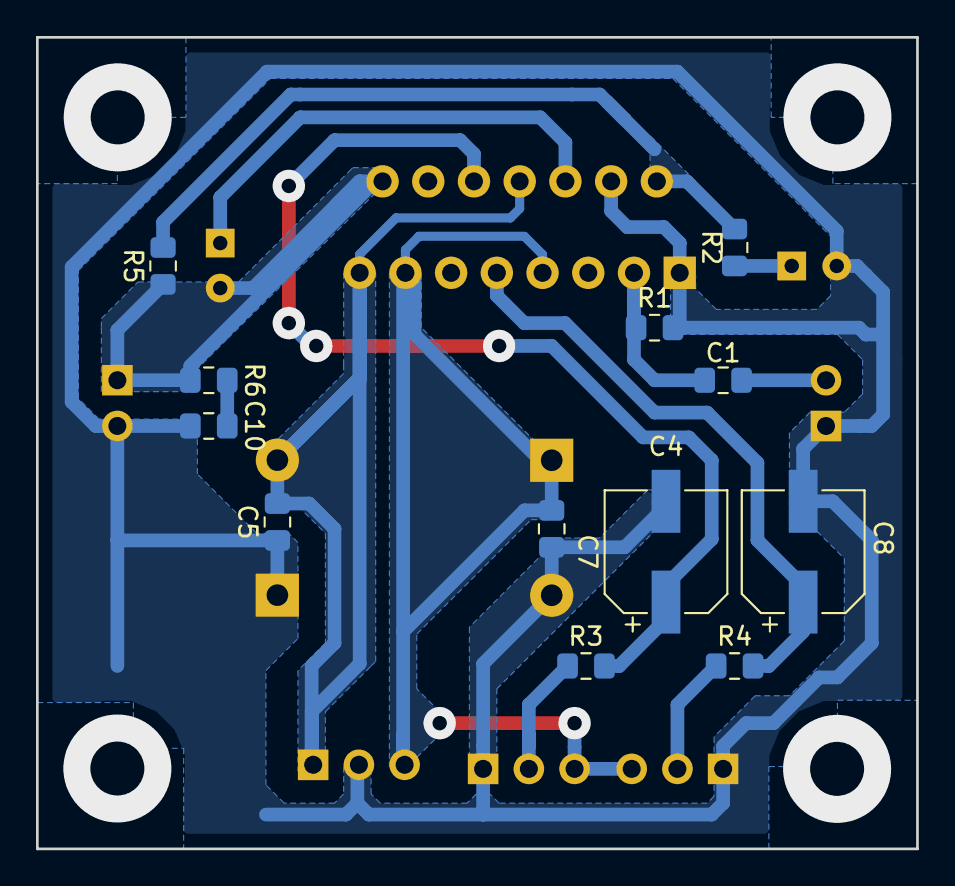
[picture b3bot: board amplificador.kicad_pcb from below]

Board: 2 copper layers, 48.9 x 45.1 mm, 22 parts (12 on the bottom side), 14 nets.

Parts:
C1: 470nF; C_0805_2012Metric_Pad1.15x1.40mm_HandSolder
C2, C9: 22uF; CP_Radial_D5.0mm_P2.50mm
C3: CP_Small; CP_Radial_D13.0mm_P7.50mm
C4, C5: 1000uF; C_0805_2012Metric_Pad1.15x1.40mm_HandSolder
C6: 1000uF; CP_Radial_D13.0mm_P7.50mm
C7, C8: 10uF; CP_Elec_6.3x5.4
C10: 100nF; C_0805_2012Metric_Pad1.15x1.40mm_HandSolder
J1: in; PinHeader_1x02_P2.54mm_Vertical
J2: Vs; PinHeader_1x03_P2.54mm_Horizontal
J3, J4: Vs; PinHeader_1x03_P2.54mm_Vertical
J5: out; PinHeader_1x02_P2.54mm_Vertical
R1: 22k; R_0805_2012Metric_Pad1.15x1.40mm_HandSolder
R2: 680; R_0805_2012Metric_Pad1.15x1.40mm_HandSolder
R3, R4, R5, R6: R_Small_US; R_0805_2012Metric_Pad1.15x1.40mm_HandSolder
U1: TDA7294; TO-220-15_P2.54x2.54mm_StaggerOdd_Lead4.58mm_Vertical

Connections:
+15V: C3.1, C4.1, J2.3, J3.3, J4.3, U1.7, U1.13
-15V: C5.2, C6.2, J2.1, U1.8, U1.15
/MUTE: J4.2, R3.1
/STAND-BY: J3.2, R4.1
/Vin: C1.1, J1.2
/Vout: C9.2, J5.1, R5.1, R6.1, U1.14
GND: C2.2, C3.2, C4.2, C5.1, C6.1, C7.2, C8.2, C10.1, J1.1, J2.2, J3.1, J4.1, J5.2, R1.2, U1.1, U1.4
unnamed: C1.2, R1.1, U1.3
unnamed: C2.1, R2.2
unnamed: C7.1, R3.2, U1.10
unnamed: C8.1, R4.2, U1.9
unnamed: C9.1, U1.6
unnamed: C10.2, R6.2
unnamed: R2.1, R5.2, U1.2

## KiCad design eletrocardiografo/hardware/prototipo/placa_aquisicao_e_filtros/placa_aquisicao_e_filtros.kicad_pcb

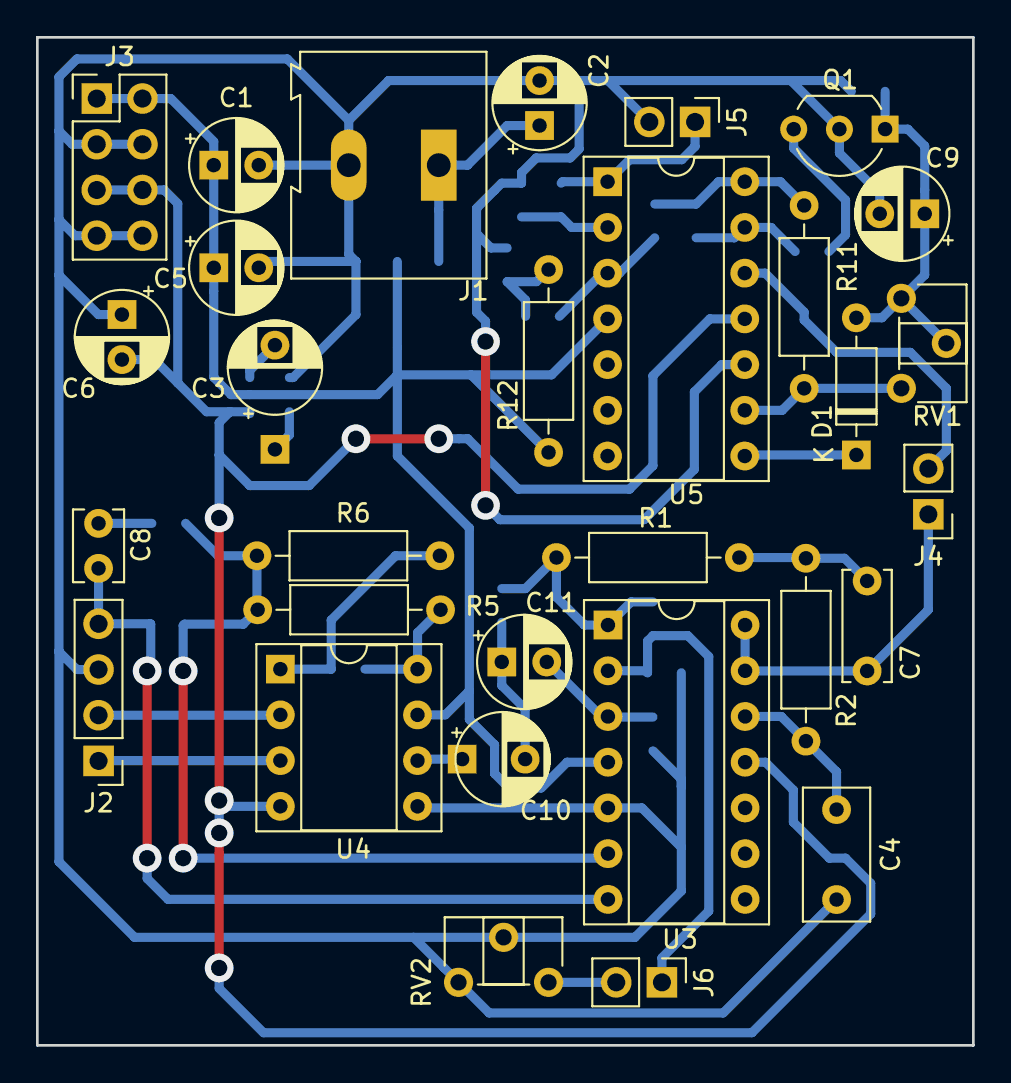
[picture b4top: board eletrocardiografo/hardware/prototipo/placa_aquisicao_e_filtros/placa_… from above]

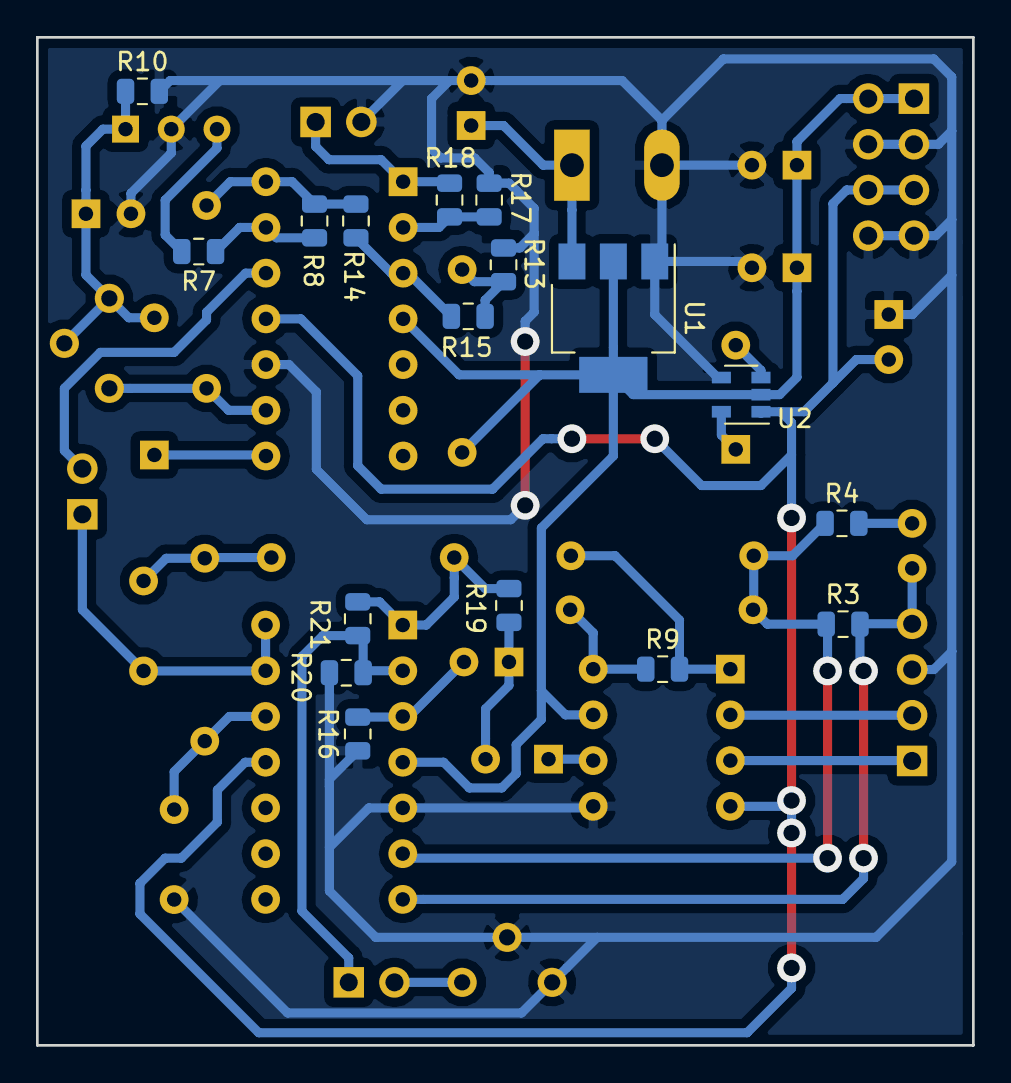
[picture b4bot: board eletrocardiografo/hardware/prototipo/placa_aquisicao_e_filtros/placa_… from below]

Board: 2 copper layers, 52.0 x 56.0 mm, 47 parts (17 on the bottom side), 33 nets.

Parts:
C1, C3, C6: 1u; CP_Radial_D5.0mm_P2.50mm
C2, C5: 10u; CP_Radial_D5.0mm_P2.50mm
C4: 47n; C_Rect_L7.2mm_W3.5mm_P5.00mm_FKS2_FKP2_MKS2_MKP2
C7: 100n; C_Disc_D6.0mm_W2.5mm_P5.00mm
C8: 100p; C_Disc_D3.8mm_W2.6mm_P2.50mm
C9: 22u; CP_Radial_D5.0mm_P2.50mm
C10, C11: 47u; CP_Radial_D5.0mm_P2.50mm
D1: 1N4148; D_DO-35_SOD27_P7.62mm_Horizontal
J1: Conn_01x02; TerminalBlock_Altech_AK300-2_P5.00mm
J2: Conn_01x04; PinHeader_1x04_P2.54mm_Vertical
J3: Conn_02x04_Counter_Clockwise; PinHeader_2x04_P2.54mm_Vertical
J4, J5, J6: Conn_01x02; PinHeader_1x02_P2.54mm_Vertical
Q1: BF245B; TO-92_Inline_Wide
R1: 18k; R_Axial_DIN0207_L6.3mm_D2.5mm_P10.16mm_Horizontal
R2: 30k; R_Axial_DIN0207_L6.3mm_D2.5mm_P10.16mm_Horizontal
R3: 1M; R_0805_2012Metric
R4, R8, R17, R18: 12k; R_0805_2012Metric
R5, R6: 24k; R_Axial_DIN0207_L6.3mm_D2.5mm_P10.16mm_Horizontal
R7: 560R; R_0805_2012Metric
R9: 75R; R_0805_2012Metric
R10, R19: 100k; R_0805_2012Metric
R11: 200k; R_Axial_DIN0207_L6.3mm_D2.5mm_P10.16mm_Horizontal
R12: 51k; R_Axial_DIN0207_L6.3mm_D2.5mm_P10.16mm_Horizontal
R13: 22k; R_0805_2012Metric
R14, R15: 1k; R_0805_2012Metric
R16: 47k; R_0805_2012Metric
R20: 68k; R_0805_2012Metric
R21: 150k; R_0805_2012Metric
RV1: 470k; Potentiometer_ACP_CA6-H2,5_Horizontal
RV2: R_POT; Potentiometer_ACP_CA6-H2,5_Horizontal
U1: AP1117-33; SOT-223-3_TabPin2
U2: TPS60401; SOT-23-5
U3, U5: Opamp_Quad_Generic; DIP-14_W7.62mm_Socket
U4: AD620; DIP-8_W7.62mm_Socket

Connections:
+3V3: C1.1, C5.1, J3.1, J3.2, R12.1, U1.2, U2.2, U3.4, U4.7, U5.4
+Vin: C2.1, J1.1, U1.3
-3V3: C6.2, J3.5, J3.6, U2.1, U3.11, U4.4, U5.11
AGC: C7.1, J4.1, U3.13, U3.14
GNDA: C1.2, C2.2, C4.2, C5.2, C6.1, C9.2, J1.2, J2.3, J3.3, J3.4, J3.7, J3.8, J5.2, Q1.2, R10.2, R13.2, R16.1, R17.2, R20.2, RV2.1, RV2.2, U1.1, U2.4, U3.5, U4.5, U5.10
HP: C10.1, U4.6
LP: R1.2, R19.2, R21.1, U3.1
unnamed: C3.1, U2.5
unnamed: C3.2, U2.3
unnamed: C4.1, R2.1, U3.12
unnamed: C7.2, R1.1, R2.2
unnamed: C8.1, R4.2
unnamed: C9.1, D1.2, Q1.1, R10.1, RV1.1, RV1.2
unnamed: C10.2, C11.1, R19.1
unnamed: C11.2, R16.2, U3.3
unnamed: D1.1, U5.8
unnamed: J4.2, U5.12
unnamed: J6.1, R20.1, R21.2, U3.2
unnamed: J6.2, RV2.3
unnamed: Q1.3, R7.2
unnamed: R3.1, R4.1, R5.2, R6.1, U3.6
unnamed: R5.1, R9.1, U4.8
unnamed: R6.2, R9.2, U4.1
unnamed: R7.1, R8.2, U5.13
unnamed: R11.1, RV1.3, U5.9
unnamed: R12.2, R13.1, R15.2
unnamed: R14.1, R15.1, U5.3
unnamed: R17.1, R18.2, U5.2
OUT: J5.1, R18.1, U5.1
SUM: R8.1, R11.2, R14.2, U5.14
left_electrode: J2.1, U4.3
ref_electrode: C8.2, J2.4, R3.2, U3.7
right_electrode: J2.2, U4.2

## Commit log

2019-08-17 add projects
2019-08-26 add monitoramento_sono
